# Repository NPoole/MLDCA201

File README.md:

# MLDCA201
Open Hardware Electronic Melodica

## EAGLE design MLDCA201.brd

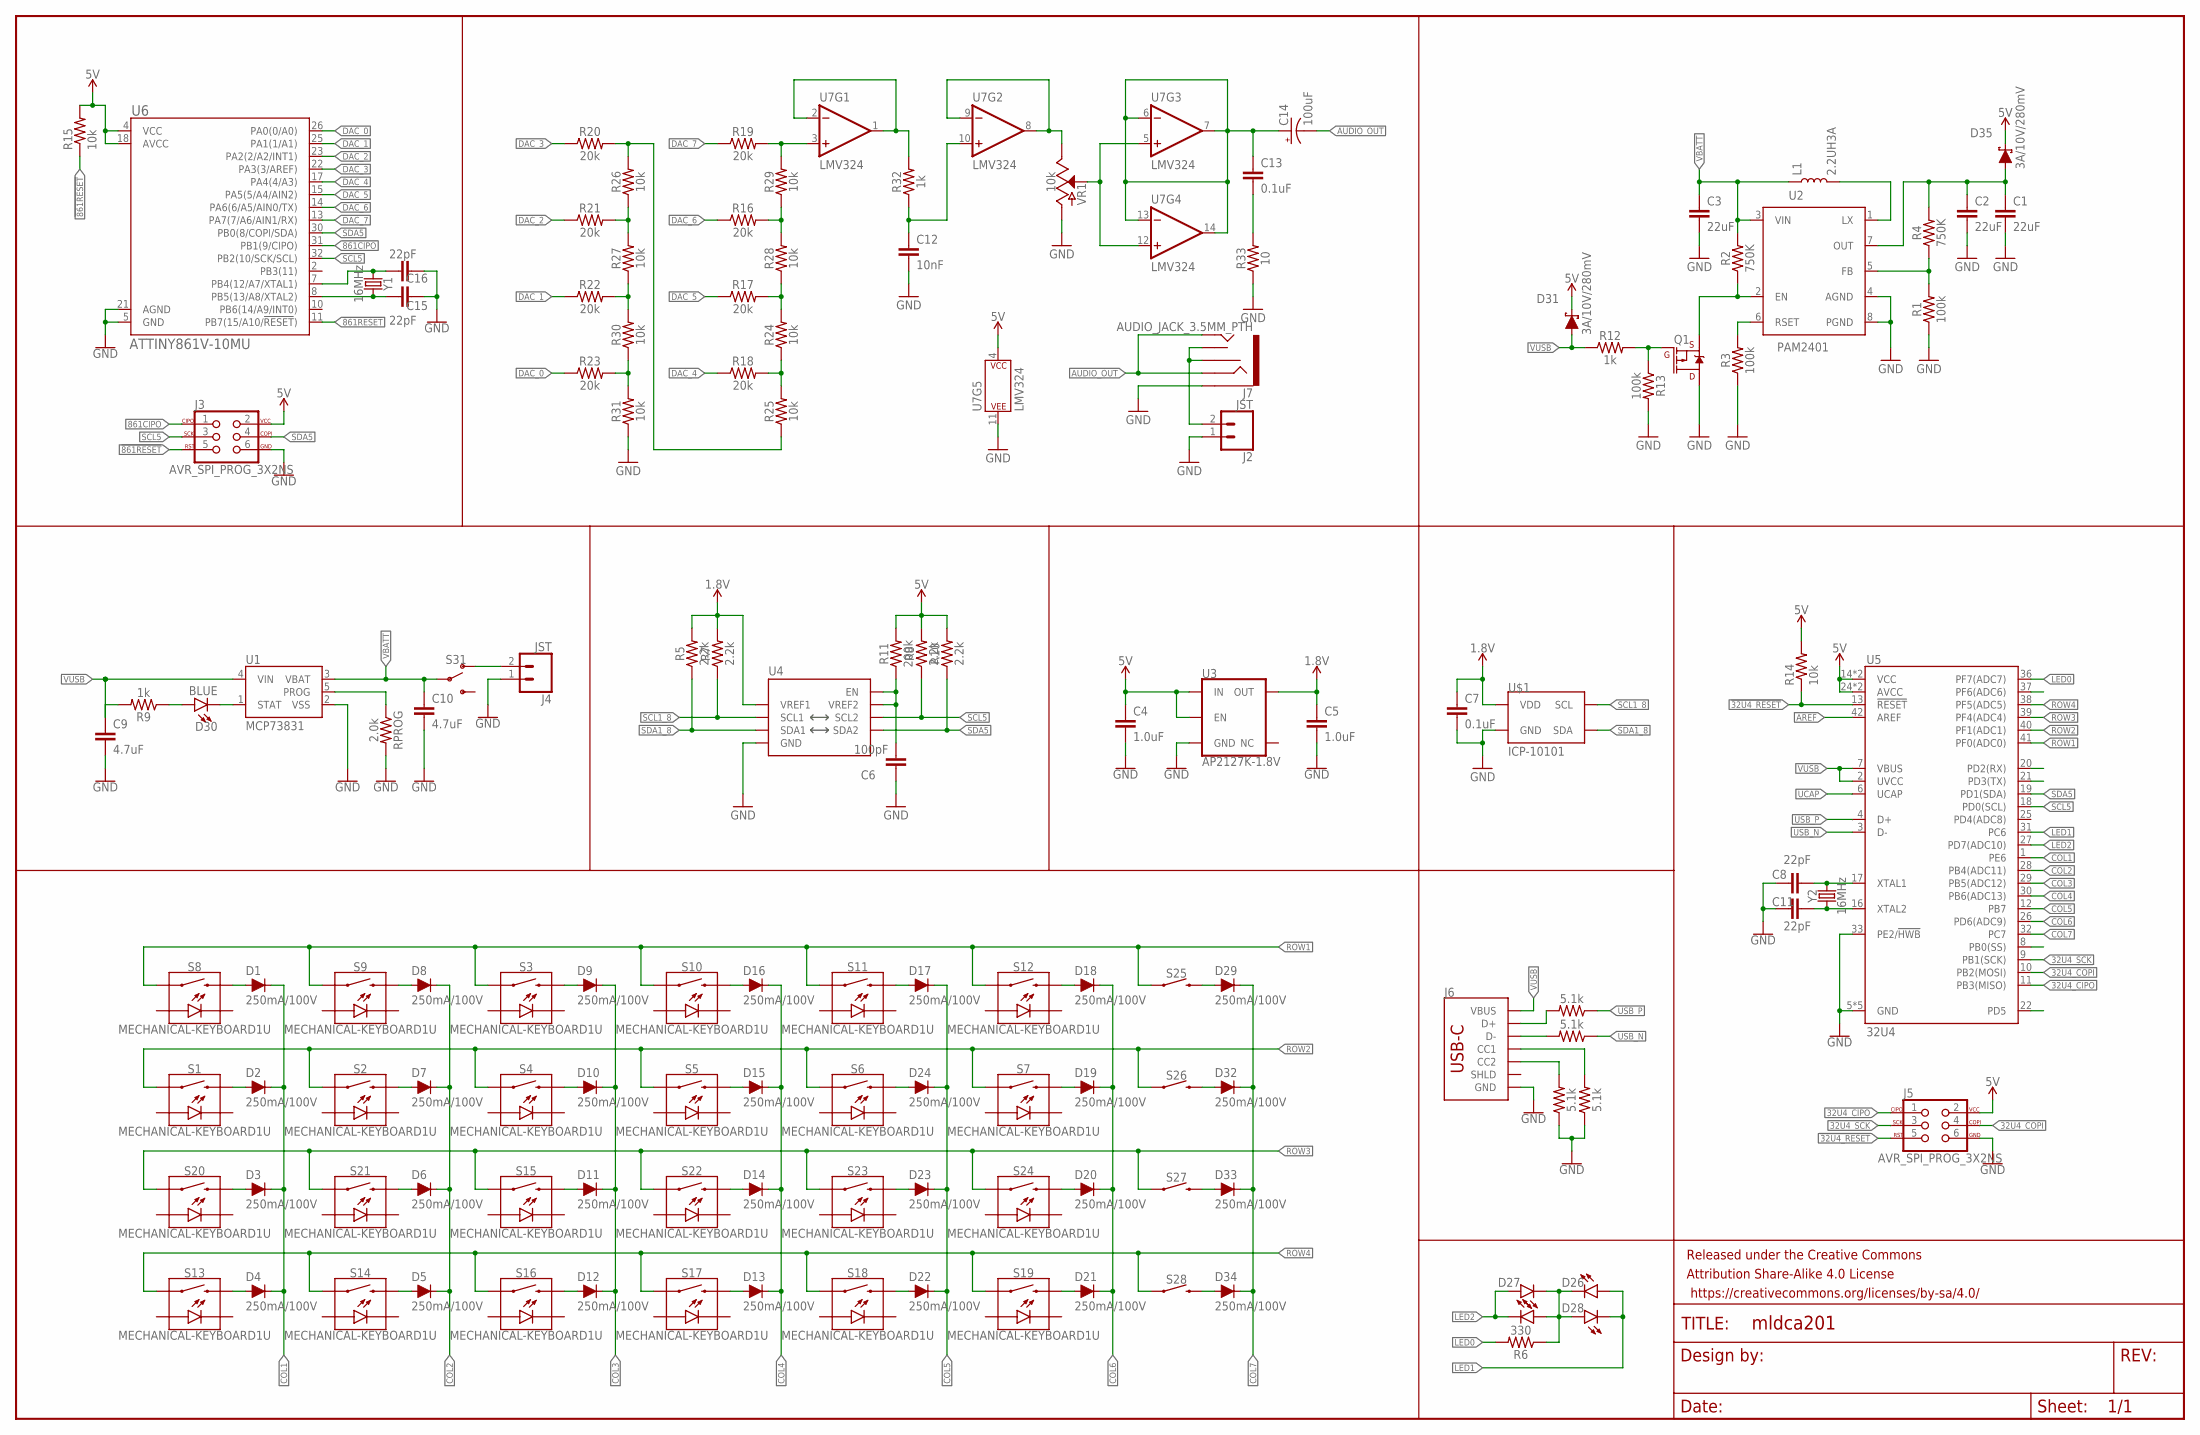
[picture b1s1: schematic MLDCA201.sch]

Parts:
C1, C2, C3: 22uF; 0805
C4, C5: 1.0uF; 0603
C6: 100pF; 0603
C7, C13: 0.1uF; 0603
C8, C11, C15, C16: 22pF; 0603
C9, C10: 4.7uF; 0603
C12: 10nF; 0603
C14: 100uF; PANASONIC_D
D1, D2, D3, D4, D5, D6, D7, D8, D9, D10, D11, D12, D13, D14, D15, D16, D17, D18, D19, D20, D21, D22, D23, D24, D29, D32, D33, D34: 250mA/100V; SOD-323@1
D25, D26, D27, D28: RED; LED-0603@1
D30: BLUE; LED-0603@1
D31, D35: 3A/10V/280mV; SOD-323
FRAME1: FRAME-LEDGER; CREATIVE_COMMONS
J2, J4: JST; JST-2-SMD
J3, J5: AVR_SPI_PROG_3X2NS; 2X3-NS
J6: USB_C_2-LAYER_PADS; USB-C-16P-2LAYER-PADS
J7: AUDIO_JACK_3.5MM_PTH; AUDIO-JACK
L1: 2.2UH3A; INDUCTOR_4X4MM
Q1: 100mA/20V/3.8Ω; SOT-416FL
R1, R3, R13: 100k; 0603
R2, R4: 750K; 0603
R5, R7, R8, R10: 2.2k; 0603
R6: 330; 0603
R9, R12, R32: 1k; 0603
R11: 200k; 0603
R14, R15, R24, R25, R26, R27, R28, R29, R30, R31: 10k; 0603
R16, R17, R18, R19, R20, R21, R22, R23: 20k; 0603
R33: 10; 0603
R34, R35, R36, R37: 5.1k; 0603
RPROG: 2.0k; 0603
S1, S2, S3, S4, S5, S6, S7, S8, S9, S10, S11, S12, S13, S14, S15, S16, S17, S18, S19, S20, S21, S22, S23, S24: MECHANICAL-KEYBOARD1U; CHERRY-MX-LED-1U
S25, S26, S27, S28: MOMENTARY-SWITCH-SPST-SMD-5.2MM-TALL; TACTILE_SWITCH_SMD_5.2MM
S31: SWITCH-SPDT-SMD-RIGHT-ANGLE; SWITCH_SPST_SMD_A
U1: MCP73831; SOT23-5
U2: PAM2401; MSOP8
U3: AP2127K-1.8V; SOT23-5
U4: PCA9306VSSOP_8PIN; VSSOP_8PIN
U5: 32U4; QFN-44-NOPAD_1:1-LESS_PASTE
U6: ATTINY861V-10MU; 32M1-A_ATM
U7: LMV324; SO14
U$1: ICP-10101
VR1: 10k; SLIDER-SMALL
Y1, Y2: 16MHz; CRYSTAL-SMD-2.0X1.6MM

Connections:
1.8V: C5.1, C7.1, R5.2, R7.2, U3.5 (OUT), U4.P2 (VREF1), U$1.5 (VDD), U$1.6 (VDD), U$1.10 (VDD)
5V: C4.1, D31.C, D35.C, J3.2, J5.2, R8.2, R10.2, R11.2, R14.2, R15.2, U3.1 (IN), U3.3 (EN), U5.14 (VCC), U5.24 (AVCC), U5.34 (VCC), U5.44 (AVCC), U6.4 (VCC), U6.18 (AVCC), U7.4 (P$V+)
32U4_CIPO: J5.1, U5.11 (PB3(MISO))
32U4_COPI: J5.4, U5.10 (PB2(MOSI))
32U4_SCK: J5.3, U5.9 (PB1(SCK))
861CIPO: J3.1, U6.31 (PB1(9/CIPO))
!32U4_RESET: J5.5, R14.1, U5.13 (!RESET)
!861RESET: J3.5, R15.1, U6.11 (PB7(15/A10/!RESET!))
AREF: U5.42 (AREF)
AUDIO_OUT: C14.-, J7.RING, J7.TIP
COL1: D1.C, D2.C, D3.C, D4.C, U5.1 (PE6)
COL2: D5.C, D6.C, D7.C, D8.C, U5.28 (PB4(ADC11))
COL3: D9.C, D10.C, D11.C, D12.C, U5.29 (PB5(ADC12))
COL4: D13.C, D14.C, D15.C, D16.C, U5.30 (PB6(ADC13))
COL5: D17.C, D22.C, D23.C, D24.C, U5.12 (PB7)
COL6: D18.C, D19.C, D20.C, D21.C, U5.26 (PD6(ADC9))
COL7: D29.C, D32.C, D33.C, D34.C, U5.32 (PC7)
DAC_0: R23.1, U6.26 (PA0(0/A0))
DAC_1: R22.1, U6.25 (PA1(1/A1))
DAC_2: R21.1, U6.23 (PA2(2/A2/INT1))
DAC_3: R20.1, U6.22 (PA3(3/AREF))
DAC_4: R18.1, U6.17 (PA4(4/A3))
DAC_5: R17.1, U6.15 (PA5(5/A4/AIN2))
DAC_6: R16.1, U6.14 (PA6(6/A5/AIN0/TX))
DAC_7: R19.1, U6.13 (PA7(7/A6/AIN1/RX))
DAC_OUT: R19.2, R29.2, U7.3 (+IN)
EN: Q1.2 (S), R2.1, U2.2 (EN)
GND: C1.2, C2.2, C3.2, C4.2, C5.2, C6.1, C7.2, C8.2, C9.2, C10.2, C11.2, C12.2, C15.2, C16.2, J2.1 (2), J3.6, J4.1 (2), J5.6, J6.GND, J6.GND2 (GND), J7.SLEEVE, Q1.3 (D), R1.1, R3.1, R13.2, R31.1, R33.1, R34.1, R35.1, RPROG.2, U1.2 (VSS), U2.4 (AGND), U2.8 (PGND), U3.2 (GND), U4.P1 (GND), U5.5 (GND), U5.15 (GND), U5.23 (GND), U5.33 (PE2/!HWB), U5.35 (GND), U5.43 (GND), U6.5 (GND), U6.21 (AGND), U7.11 (P$V-), U$1.3 (GND), U$1.8 (GND), U$1.9 (GND), VR1.BOTTOM (A)
LED0: R6.2, U5.36 (PF7(ADC7))
LED1: D26.A, D28.C, U5.31 (PC6)
LED2: D25.A, D27.C, U5.27 (PD7(ADC10))
unnamed: RPROG.1, U1.5 (PROG)
unnamed: D30.C, U1.1 (STAT)
unnamed: J4.2 (1), S31.1 (O)
unnamed: D30.A, R9.1
unnamed: D1.A, S8.S2 (2)
unnamed: D2.A, S1.S2 (2)
unnamed: D3.A, S20.S2 (2)
unnamed: D4.A, S13.S2 (2)
unnamed: D5.A, S14.S2 (2)
unnamed: D6.A, S21.S2 (2)
unnamed: D7.A, S2.S2 (2)
unnamed: D8.A, S9.S2 (2)
unnamed: D9.A, S3.S2 (2)
unnamed: D10.A, S4.S2 (2)
unnamed: D11.A, S15.S2 (2)
unnamed: D12.A, S16.S2 (2)
unnamed: D13.A, S17.S2 (2)
unnamed: D14.A, S22.S2 (2)
unnamed: D15.A, S5.S2 (2)
unnamed: D16.A, S10.S2 (2)
unnamed: D17.A, S11.S2 (2)
unnamed: D24.A, S6.S2 (2)
unnamed: D23.A, S23.S2 (2)
unnamed: D22.A, S18.S2 (2)
unnamed: D21.A, S19.S2 (2)
unnamed: D20.A, S24.S2 (2)
unnamed: D19.A, S7.S2 (2)
unnamed: D18.A, S12.S2 (2)
unnamed: R1.2, R4.1, U2.5 (FB)
unnamed: L1.P$2 (2), U2.1 (LX)
unnamed: R3.2, U2.6 (RSET)
unnamed: D29.A, S25.3 (2)
unnamed: D32.A, S26.3 (2)
unnamed: Q1.1 (G), R12.2, R13.1
unnamed: D33.A, S27.3 (2)
unnamed: D34.A, S28.3 (2)
unnamed: D25.C, D26.C, D27.A, D28.A, R6.1
unnamed: C6.2, R11.1, U4.P7 (VREF2), U4.P8 (EN)
unnamed: C1.1, C2.1, D35.A, R4.2, U2.7 (OUT)
unnamed: C11.1, U5.16 (XTAL2), Y2.1
unnamed: C8.1, U5.17 (XTAL1), Y2.3 (2)
unnamed: U7.8 (OUT), U7.9 (-IN), VR1.TOP (E)
unnamed: R16.2, R28.2, R29.1
unnamed: R17.2, R24.2, R28.1
unnamed: R18.2, R24.1, R25.2
unnamed: R20.2, R25.1, R26.2
unnamed: R21.2, R26.1, R27.2
unnamed: R22.2, R27.1, R30.2
unnamed: R23.2, R30.1, R31.2
unnamed: R32.2, U7.1 (OUT), U7.2 (-IN)
unnamed: C12.1, R32.1, U7.10 (+IN)
unnamed: U7.5 (+IN), U7.12 (+IN), VR1.WIPER (S)
unnamed: C13.1, C14.+, U7.6 (-IN), U7.7 (OUT), U7.13 (-IN), U7.14 (OUT)
unnamed: C13.2, R33.2
unnamed: J6.A5 (CC1), R35.2
unnamed: J6.B5 (CC2), R34.2
unnamed: J6.A6 (D+), J6.B6 (D+), R36.2
unnamed: J6.A7 (D-), J6.B7 (D-), R37.2
unnamed: C16.1, U6.7 (PB4(12/A7/XTAL1)), Y1.1
unnamed: C15.1, U6.8 (PB5(13/A8/XTAL2)), Y1.3 (2)
unnamed: J2.2 (1), J7.RSH, J7.TSH
ROW1: S3.S1 (1), S8.S1 (1), S9.S1 (1), S10.S1 (1), S11.S1 (1), S12.S1 (1), S25.1, U5.41 (PF0(ADC0))
ROW2: S1.S1 (1), S2.S1 (1), S4.S1 (1), S5.S1 (1), S6.S1 (1), S7.S1 (1), S26.1, U5.40 (PF1(ADC1))
ROW3: S15.S1 (1), S20.S1 (1), S21.S1 (1), S22.S1 (1), S23.S1 (1), S24.S1 (1), S27.1, U5.39 (PF4(ADC4))
ROW4: S13.S1 (1), S14.S1 (1), S16.S1 (1), S17.S1 (1), S18.S1 (1), S19.S1 (1), S28.1, U5.38 (PF5(ADC5))
SCL1_8: R7.1, U4.P3 (SCL1), U$1.2 (SCL)
SCL5: J3.3, R8.1, U4.P6 (SCL2), U5.18 (PD0(SCL)), U6.32 (PB2(10/SCK/SCL))
SDA1_8: R5.1, U4.P4 (SDA1), U$1.4 (SDA)
SDA5: J3.4, R10.1, U4.P5 (SDA2), U5.19 (PD1(SDA)), U6.30 (PB0(8/COPI/SDA))
TXLED: U5.22 (PD5)
UCAP: U5.6 (UCAP)
USB_N: R37.1, U5.3 (D-)
USB_P: R36.1, U5.4 (D+)
VBATT: C3.1, C10.1, L1.P$1 (1), R2.2, S31.2, U1.3 (VBAT), U2.3 (VIN)
VUSB: C9.1, D31.A, J6.VBUS1 (VBUS), J6.VBUS2 (VBUS), R9.2, R12.1, U1.4 (VIN), U5.2 (UVCC), U5.7 (VBUS)

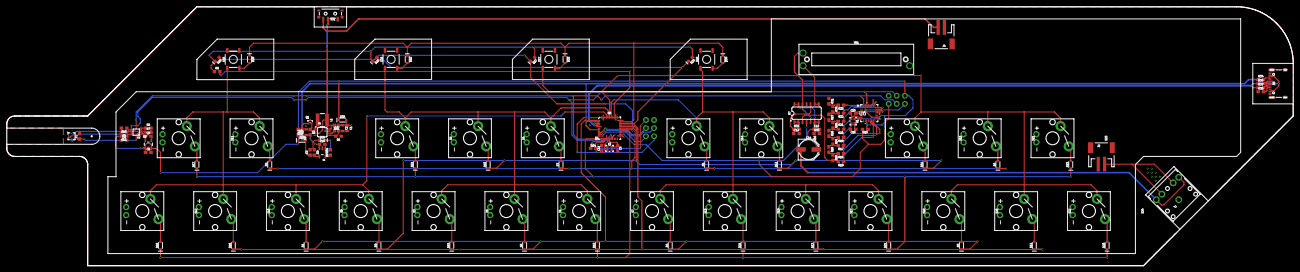
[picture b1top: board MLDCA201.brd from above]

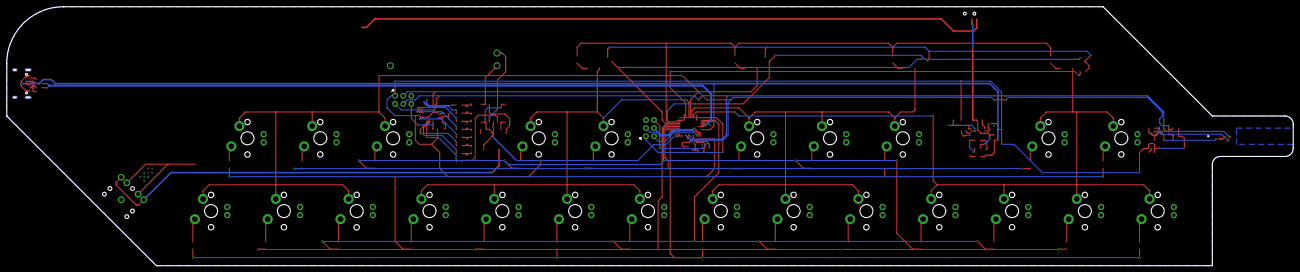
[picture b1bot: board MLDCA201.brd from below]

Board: 2 copper layers, 403.9 x 81.3 mm, 138 parts (2 on the bottom side), 103 nets.

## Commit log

2021-11-06 Initial Commit v0.01

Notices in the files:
parts and their libraries:
SparkFun-Switches: Licensing: Creative Commons ShareAlike 4.0 International - https://creativecommons.org/licenses/by-sa/4.0
SparkFun-Capacitors: Licensing: CC v3.0 Share-Alike You are welcome to use this library for commercial purposes.
SparkFun-Aesthetics: Released under the Creative Commons
